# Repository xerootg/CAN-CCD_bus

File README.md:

CAN->CCD Bus Translator V2
===========================

I am designing an interface for my current engine swap project in my Jeep. I am starting with a 1998 Jeep Cherokee, 4.0L I6, AX15 manual transmission, and a NP242 transfer case, and I am replacing the engine with a VW TDI from a 2005 VW Passat (2.0L 8v, code:                                                                                                                                                                                                                                                                                                                                                                                                                                                                                                                                                                                                                                                                                                                                                                                                                                                                                            BHW) and a 6 speed manual from a late model TJ Rubicon (NSG370).

This project is made up of two parts:
* a board designed to interface with the Jeep CCD protocol and VW CAN v2.0
* a event driven application to handle the needed events to translate between buses

Things needed to get started:
----------------------------
* KiCAD
* PlatformIO
* MinGW or GCC installed and on your $PATH (for tests)

Hardware Concept
----------------
* Teensy 3.2 at the core - extra I/O available for further expansion
* dedicated CCD interface IC - CDP68HC68S1
* CAN handled by teensy/MPC2551
* I/O for all circuits missing from engine/Jeep
* [BOM at Mouser](https://www.mouser.com/ProjectManager/ProjectDetail.aspx?AccessID=2fd919600a)

The VW ECU expects a handful of things the Jeep does not handled
* fuel level (leters)
* speed at 8200 pulses/mile (need to confirm voltage EDC expects)
* cruise control is array of switches
* alternator is monitored by gauge cluster

Likewise, the Jeep expects a couple things the VW ECU does not provide
* speed at 8000 pulses/mile from VSS, CCD expects 8388 bits/mile for odometer
* oil pressure (PSI)
* fuel level (%)
* cruise control is resistor bus
* glow plug lamp needs CAN->physical output translation

Software Concept
----------------
* Unit tests are written in unity syntax
* Events are handled by Eventually
* Arduino API does hardware interface, with TeensyDuino additions
* Each interface gets its own class: CCD, CAN, distance/speed, fuel level... etc.

To run tests, run `pio test -e native`
To compile ELF for teensy, run `pio run`

I'm a web developer so this is gonna be MVCish. 
- Model: Holds some state
- View: Puts state, I.E. does the actual interface with HW
- Controller: translates between model and view, and viceversa

The counter class implements logic to read the hardware model, so by this definition it is a Controller.
The VehicleState class is just a holder of state, so it is squarely a Model.
The CCD hardware interface gets/sets values on the HardwareSerial interface, so it is a view.

This will likely morph.

TODO
----

* implement CAN class
* implement fuel level
* translate cruise buttons
* rewrite CCD class to respect bus status (currently it blindly transmits)
* write tests so they can run on teensy

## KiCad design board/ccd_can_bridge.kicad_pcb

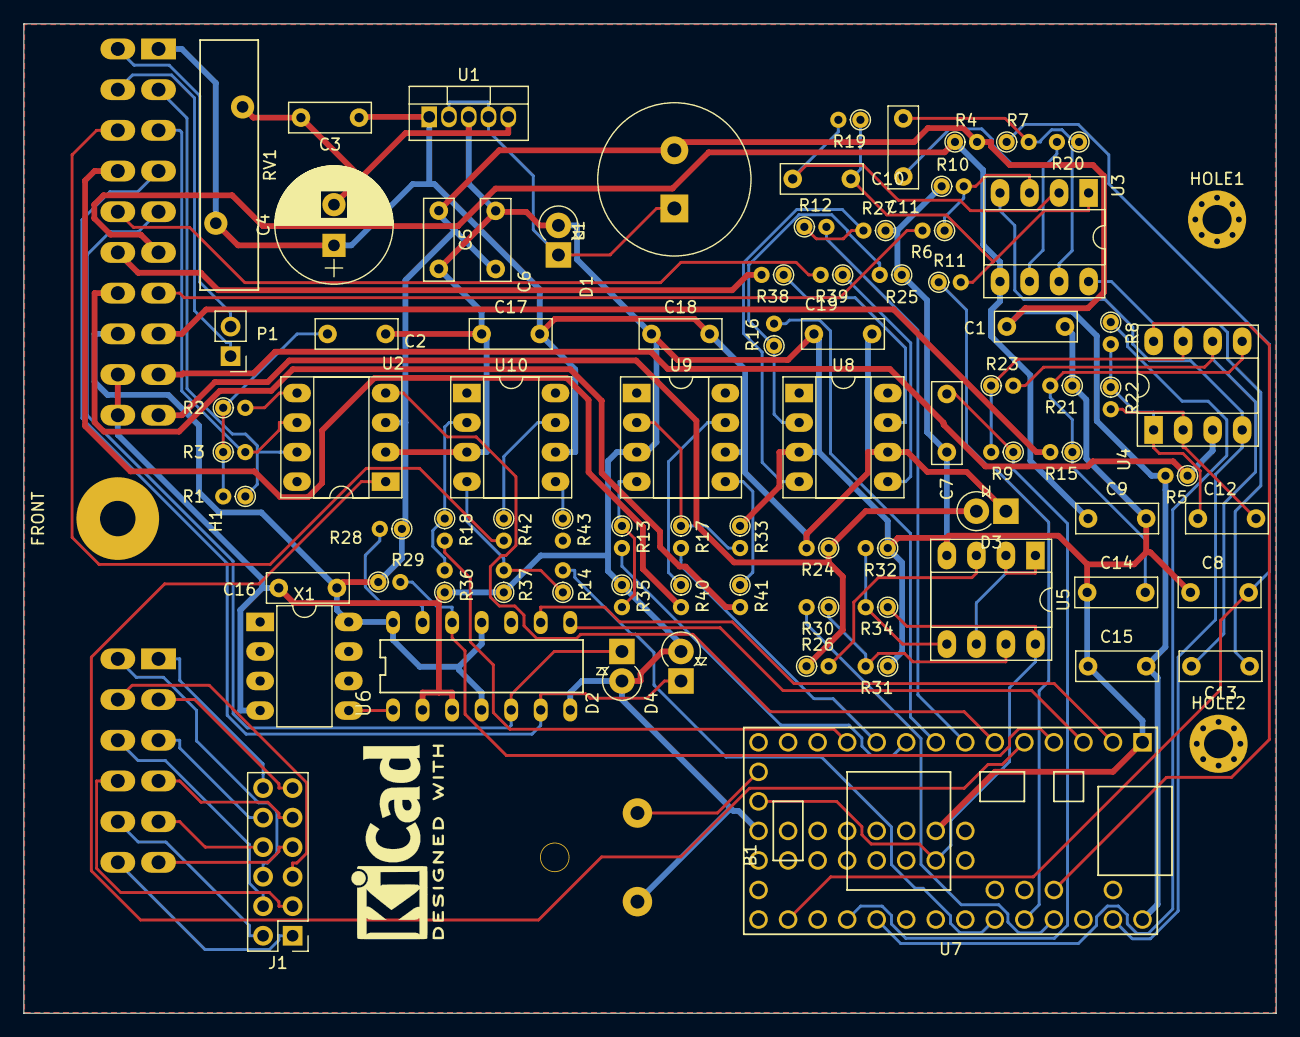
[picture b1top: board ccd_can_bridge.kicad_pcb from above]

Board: 2 copper layers, 107.7 x 85.1 mm, 85 parts (0 on the bottom side), 82 nets.

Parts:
B1: 1066; keystone_1067
C1, C3, C6, C17, C18, C19: 0.1uF; C_Disc_D7.0mm_W2.5mm_P5.00mm
C2: 4700pF; C_Disc_D7.0mm_W2.5mm_P5.00mm
C4: 100uF; CP_Radial_D10.0mm_P3.50mm
C5: 100uF; C_Disc_D7.0mm_W2.5mm_P5.00mm
C7, C8, C9, C10, C11, C12, C13, C14: 10uF; C_Disc_D7.0mm_W2.5mm_P5.00mm
C15, C16: C; C_Disc_D7.0mm_W2.5mm_P5.00mm
D1: 1N5819; D_DO-41_SOD81_P2.54mm_Vertical_KathodeUp
D2, D4: 1N4728; D_DO-41_SOD81_P2.54mm_Vertical_KathodeUp
D3: D; D_DO-41_SOD81_P2.54mm_Vertical_KathodeUp
H1: Modice_ME-MX_32; modice_ME-MX-32-position
HOLE1, HOLE2: MountingHole_2.5mm_Pad_Via
J1: CONN_01X12; Pin_Header_Straight_2x06_Pitch2.54mm
L1: 100uH; Inductor_Radial_D13.0mm_P5.00mm
P1: CONN_01X02; Pin_Header_Straight_1x02_Pitch2.54mm
R1, R3: 60; R_Axial_DIN0204_L3.6mm_D1.6mm_P1.90mm_Vertical
R2: 300; R_Axial_DIN0204_L3.6mm_D1.6mm_P1.90mm_Vertical
R4, R5: 130; R_Axial_DIN0204_L3.6mm_D1.6mm_P1.90mm_Vertical
R6, R15: 560; R_Axial_DIN0204_L3.6mm_D1.6mm_P1.90mm_Vertical
R7, R8, R9, R10, R11, R19, R20, R21, R22, R23, R25, R27, R30, R31, R33, R35, R36, R37: 1k; R_Axial_DIN0204_L3.6mm_D1.6mm_P1.90mm_Vertical
R12, R13, R14, R16, R17, R18: 20; R_Axial_DIN0204_L3.6mm_D1.6mm_P1.90mm_Vertical
R24, R26, R28, R29: 10k; R_Axial_DIN0204_L3.6mm_D1.6mm_P1.90mm_Vertical
R32: 37k; R_Axial_DIN0204_L3.6mm_D1.6mm_P1.90mm_Vertical
R34: 15k; R_Axial_DIN0204_L3.6mm_D1.6mm_P1.90mm_Vertical
R38, R39, R40, R41, R42, R43: 100; R_Axial_DIN0204_L3.6mm_D1.6mm_P1.90mm_Vertical
RV1: ERZ-V20D220; RV_Disc_D21.5_W5_P10
U1: LM2576HVS-5.0/NOPB; TO-220-5_Pentawatt_Multiwatt-5_Vertical
U2: MCP2561; DIP-8_W7.62mm_Socket_LongPads
U3, U4, U5: MCP6002; DIP-8_W7.62mm_Socket_LongPads
U6: CDP68HC68S1
U7: Teensy3.2; Teensy30_31_32_LC
U8, U9, U10: TC4427; DIP-8_W7.62mm_Socket_LongPads
X1: OSCILLATOR-VDD-4; DIP-8_W7.62mm_LongPads

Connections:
+3V3: R34.1, U5.8, U7.16, U7.50
+12V: C3.1, C4.1, C17.2, C18.2, C19.2, D3.1, H1.1, R24.2, RV1.1, U1.1, U8.6, U9.6, U10.6
A0_fuel_level: C8.2, R7.1, U7.21
A1_VSS_count: R11.1, U7.29
A2_oil_pressure: C7.2, R9.1, U7.23
A3_steering_wheel: R8.1, U7.24
Earth: B1.-, C1.1, C2.1, C3.2, C4.2, C5.2, C6.2, C7.1, C8.1, C9.1, C14.1, C15.2, C16.2, C17.1, C18.1, C19.1, D1.2, D2.2, D4.2, H1.19, H1.20, R10.1, R21.1, R25.1, R27.1, R31.1, R32.1, R33.1, R35.1, R36.1, R37.1, RV1.2, U1.3, U1.5, U2.2, U5.4, U6.2, U6.3, U6.7, U7.1, U7.17, U7.39, U8.3, U9.3, U10.3, X1.4
unnamed: B1.+, U7.15
unnamed: C2.2, R1.2, R2.1, R3.1
unnamed: C10.1, R11.2, R19.1, U3.1
unnamed: C10.2, R19.2, U3.2
unnamed: C11.1, R7.2, R20.1, U3.7
unnamed: C11.2, R20.2, U3.6
unnamed: C12.1, R8.2, R22.1, U4.1
unnamed: C12.2, R22.2, U4.2
unnamed: C13.1, R9.2, R23.1, U4.7
unnamed: C13.2, R23.2, U4.6
unnamed: C14.2, R15.1, R21.2, U4.5
unnamed: D1.1, L1.1, U1.2, U1.4
unnamed: H1.11, P1.2
unnamed: H1.12, P1.1
unnamed: H1.21, J1.12
unnamed: H1.22, J1.11
unnamed: H1.23, J1.10
unnamed: H1.24, J1.9
unnamed: H1.25, J1.8
unnamed: H1.26, J1.7
unnamed: H1.27, J1.6
unnamed: H1.28, J1.5
unnamed: H1.29, J1.4
unnamed: H1.30, J1.3
unnamed: H1.31, J1.2
unnamed: H1.32, J1.1
unnamed: R2.2, U2.5
unnamed: R6.1, R10.2, U3.3
unnamed: R12.1, R27.2, U8.4
unnamed: R13.1, R35.2, U9.4
unnamed: R14.1, R37.2, U10.4
unnamed: R16.1, R25.2, U8.2
unnamed: R17.1, R33.2, U9.2
unnamed: R18.1, R36.2, U10.2
unnamed: R26.2, U5.3
unnamed: R28.2, U6.13
unnamed: R30.1, R31.2, U5.7
unnamed: R32.2, R34.2, U5.5
unnamed: R38.1, U8.7
unnamed: R39.1, U8.5
unnamed: R40.1, U9.7
unnamed: R41.1, U9.5
unnamed: R42.1, U10.7
unnamed: R43.1, U10.5
unnamed: U5.1, U5.2, U5.6
unnamed: U6.1, X1.5
agnd: U3.4, U4.4, U7.32
alt_sig: R30.2, U7.30
alternator_lamp_in: D3.2, H1.10, R24.1, R26.1
aref: U3.8, U4.8, U7.35
can_rx: U2.4, U7.6
can_tx: U2.1, U7.5
canh_in: H1.2, R1.1, U2.7
canl_in: H1.3, R3.2, U2.6
ccd+: D2.1, H1.5, U6.5
ccd-: D4.1, H1.4, U6.6
cruise_en: R13.2, U7.9
cruise_enable_out: H1.17, R41.2
cruise_res: R16.2, U7.8
cruise_res_out: H1.16, R38.2
cruise_set: R12.2, U7.7
cruise_set_out: H1.15, R39.2
fuel_level_in: C9.2, H1.6, R4.1, U3.5
glowplug_lamp_out: H1.14, R40.2
gp_out: R17.2, U7.10
idle: R29.2, U6.12, U7.4
misc_out_en: R14.2, U7.28
oil_pressure_in: H1.8, R15.2
rxd: U6.9, U7.2
signal_5v_out: C1.2, C5.1, C6.1, C15.1, C16.1, H1.18, L1.2, R4.2, R5.2, R28.1, R29.1, U2.3, U6.4, U6.11, U6.14, U7.33, X1.8
steering_wheel_in: H1.9, R5.1, U4.3
txd: U6.8, U7.3
vss_in: H1.7, R6.2
vss_out: H1.13, R42.2
vss_pwm: R18.2, U7.11

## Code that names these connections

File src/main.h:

//pin definitions
#define CCD_RXD 0
#define CCD_TXD 1
#define CCD_IDLE 2 //RISING = message incoming, FALLING = message ending
#define CAN_TX 3
#define CAN_RX 4
#define CRUISE_SET_OUT 5
#define CRUISE_RESUME_OUT 6
#define CRUISE_ENABLE_OUT 7
#define GLOWPLUG_LAMP_OUT 8
#define VSS_OUT 9
#define FUEL_LEVEL_IN 14
#define OIL_PRESSURE_IN 16
#define STEERING_WHEEL_IN 17
#define ALTERNATOR_HEALTH_IN 23
#define VSS_IN 30
#define MISC_OUT 28 //TC4427 output

//Fuel level trims
#define FUEL_MAX 1023
#define FUEL_MIN 0

//oil pressure trims
#define OIL_PRESSURE_MAX 1023 //this is whatever MAX oil pressure is (ADC)
#define OIL_PRESSURE_MIN 0 //this is whatever 0 PSI is (ADC)
#define OIL_PRESSURE_SENSOR_MAX 90 //this is what the sensor pressure is at OIL_PRESSURE_MAX

bool cruiseUp = false;
bool cruiseDown = false;
bool cruiseEnabled = false;
bool cruiseSet = false;
bool cruiseCancel = false;
bool cruiseResume = false;

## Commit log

2016-06-24 CCD codes so far.
2016-06-24 Cruise light confirmed with 2001 XJ cluster.
2016-06-24 SKIM light for 1998.5 to 2001 XJ gauge clusters.
2016-06-25 Notes.
2016-06-25 Clarification.
2016-06-25 Add note about "no bus" error and add testing code.
2016-06-26 Start cleaning out test code for actual code.
2016-06-26 Some test code in here, but working on the conversion functions.
2016-06-26 Custom scaling for coolant temperature. Might have to make vehicle definitions later if they end up being different per vehicle platform.
2016-06-26 Speedometer handling.
2016-06-26 Start prototyping CCD class.
2016-06-26 More documentation and bring over update/transmit.
2016-06-26 Fix hard crash. Passing Serial1 reference into the initializer was too much for the AVR core and setup() would never fire. Example code now simulates a warmed up idling engine.
2016-06-26 Add back in the ability to send a test RPM over Serial.
2016-06-26 Add light turning on/off.
2016-06-27 Bit of documentation.
2016-06-27 Documentation fix.
2016-06-27 Take out unneeded debug.
2016-06-27 Add example GIF.
2016-06-27 Hardware information.
2016-06-27 Atmei
2016-06-28 Distance traveled calculate start.
2016-06-29 New information about that bit field.
2016-06-29 Spelling.
2016-06-30 Few standards updates and prototyping CAN abstract class.
2016-07-01 Organize.
2016-07-01 Rework.
2016-08-01 More documentation, a timing tweak, and more testing.
2016-08-02 Add another example.
2016-08-02 Rename
2016-08-04 Now with working fuel level support.
2016-08-14 License as GPLv3.
2017-02-28 Initial port to support CDP68HC68S1 SCI based communication
2017-02-28 Updating the readme for my specific implementation
2017-02-28 CDP68HC68S1 initial implementation
2017-03-01 added odometer function, distance pulses along with time also set speed. Looks like 8400 pulses to a mile.
2018-04-17 inital CAN->CCD, with initial counter class
2018-04-17 adding PCB and schematic
2018-04-17 bad pin definition, vss in is on pin 22 and misc out is on pin 21
2018-04-18 initial ISR to handle FTM for VSS
2018-04-18 mend
2018-04-19 inital tests running for the CCD class
2018-04-19 additional test setup
2018-04-19 submoduling FlexCAN into the project
2018-04-19 CAN test structure
2018-04-20 implementing a state class to hold vehicle state, restructuring tests to support it
2018-04-20 restructuring tests
2018-04-20 baselining vehicle status class
2018-04-20 modifying tests to run on Teensy as well as native
2018-04-20 adding values to C15, C16, and D3 in prep to order components. R24 needs tweaking.
2018-04-22 Adding a BOM to the readme
2018-04-24 getting a bit more organized
2018-11-17 First attempt at moving away from platformIO. Makefile needs some work yet. Submoduled all dependancies instead of depending on system install. Moved headers into include folder.
2018-11-17 additional cleanup
2018-11-17 getPinIndex is the last missing function reference
2018-11-17 getting VS Code intellisense working again
2018-11-17 getting pins_teensy into its own object
2018-11-20 cmake first attempt and introduction of VehicleState pointer
